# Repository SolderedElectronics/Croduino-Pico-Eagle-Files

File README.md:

# Croduino Pico Eagle Files
## Image

[Croduino Pico(100010)](https://e-radionica.com/en/croduino-pico.html)

## Description and details
Croduino Pico is a sequel to Croduino Basic board. It is simpler than the Basic version since it doesn't have FTDI converter on-board so it needs another board which has one for programming(Croduino Basic, for example). It is imagined to be used for leaving in projects and products.

###Specs:
- Atmega328 microcontroller(32kB flash, 2kB RAM, 0.5kB EEPROM)
- 22 I/O pins, 14 digital I/O, 6 PWM, 8 analog pins
- Size only 3 x 5cm
- LED light on the 13th pin
- Voltage regulator for possibility of external charging
- Made in Croatia (EU)
- Free lifetime technical support at techsupport@e-radionica.com
- Should be set up as "Arduino Nano w/ Atmega328" in Arduino software.

Microcontroller on-board is loaded with Arduino Optiboot bootloader.

## Repository content
This repo contains Cadsoft Eagle .sch and .brd files for Croduino Pico board. It also contains schematic in .pdf created from .sch Eagle file. 
Files have been arranged into folders for navigating between different versions of board. 
Tip: layer 200 shows top silkscreen and layer 208 should be bottom silkscreen. tParts and bParts is not used.

## Docs
- [Croduino Pico product page] (https://e-radionica.com/en/croduino-pico.html)
- [Croduino lessons - on croatian language] (https://vimeo.com/channels/croduino)

## Board versions
- v1.0 - inital version

## License info
This product is open-source. Yay!
For any tech questions, contact us at techsupport@e-radionica.com
If you find an Issue, please open one at GitHub. If you can improve our product, fork us.

e-radionica.com Team.

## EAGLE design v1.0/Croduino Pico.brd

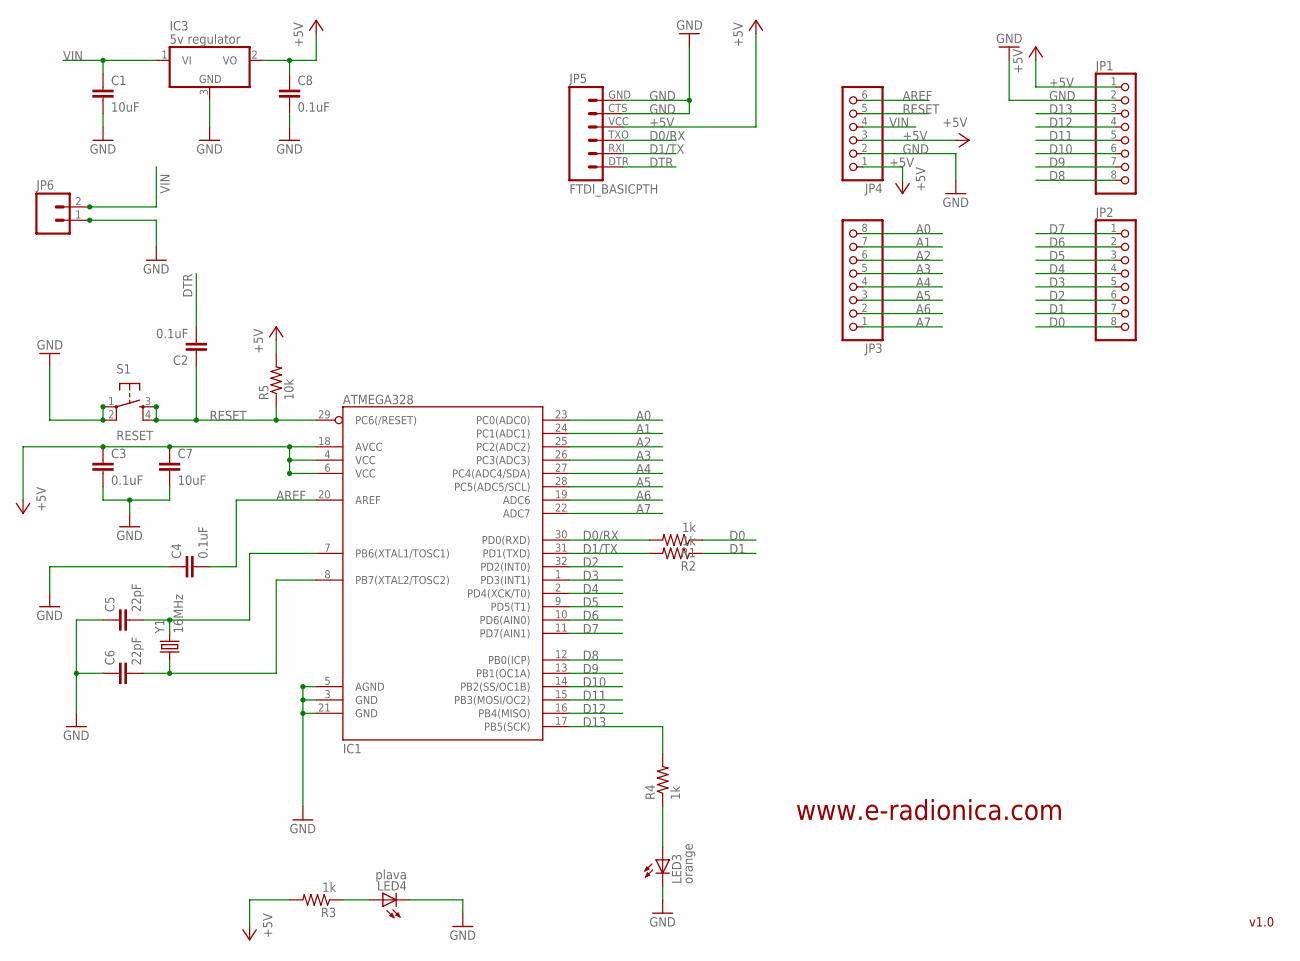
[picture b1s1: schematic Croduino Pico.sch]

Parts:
C1, C7: 10uF; C3216
C2, C3, C4, C8: 0.1uF; 0603-CAP
C5, C6: 22pF; 0603-CAP
IC1: ATMEGA328; TQFP32-08
IC3: 5v regulator; TO252
JP1, JP2, JP3: PINHD-1X8BIG; 1X08-BIG
JP4: PINHD-1X6B; 1X06-BIG
JP5: FTDI_BASICPTH; FTDI_BASIC
JP6: M02LOCK_LONGPADS; 1X02_LOCK_LONGPADS
LED3: orange; CHIP-LED0805
LED4: plava; CHIP-LED0805
R1, R2, R3, R4: 1k; 0603-RES
R5: 10k; 0603-RES
S1: RESET; TACTILE_SWITCH_SMD
Y1: 16MHz; CRYSTAL-SMD-5X3

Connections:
+5V: C3.1, C7.1, C8.1, IC1.4 (VCC), IC1.6 (VCC), IC1.18 (AVCC), IC3.2 (VO), JP1.1, JP4.1, JP4.3, JP5.VCC (4), R3.2, R5.2
A0: IC1.23 (PC0(ADC0)), JP3.8
A1: IC1.24 (PC1(ADC1)), JP3.7
A2: IC1.25 (PC2(ADC2)), JP3.6
A3: IC1.26 (PC3(ADC3)), JP3.5
A4: IC1.27 (PC4(ADC4/SDA)), JP3.4
A5: IC1.28 (PC5(ADC5/SCL)), JP3.3
A6: IC1.19 (ADC6), JP3.2
A7: IC1.22 (ADC7), JP3.1
AREF: C4.2, IC1.20 (AREF), JP4.6
CRYSTAL1: C5.2, IC1.7 (PB6(XTAL1/TOSC1)), Y1.3 (2)
CRYSTAL2: C6.2, IC1.8 (PB7(XTAL2/TOSC2)), Y1.1
D0: JP2.8, R1.1
D0/RX: IC1.30 (PD0(RXD)), JP5.TXO (3), R1.2
D1: JP2.7, R2.1
D1/TX: IC1.31 (PD1(TXD)), JP5.RXI (2), R2.2
D2: IC1.32 (PD2(INT0)), JP2.6
D3: IC1.1 (PD3(INT1)), JP2.5
D4: IC1.2 (PD4(XCK/T0)), JP2.4
D5: IC1.9 (PD5(T1)), JP2.3
D6: IC1.10 (PD6(AIN0)), JP2.2
D7: IC1.11 (PD7(AIN1)), JP2.1
D8: IC1.12 (PB0(ICP)), JP1.8
D9: IC1.13 (PB1(OC1A)), JP1.7
D10: IC1.14 (PB2(SS/OC1B)), JP1.6
D11: IC1.15 (PB3(MOSI/OC2)), JP1.5
D12: IC1.16 (PB4(MISO)), JP1.4
D13: IC1.17 (PB5(SCK)), JP1.3, R4.2
DTR: C2.2, JP5.DTR (1)
GND: C1.2, C3.2, C4.1, C5.1, C6.1, C7.2, C8.2, IC1.3 (GND), IC1.5 (AGND), IC1.21 (GND), IC3.3 (GND), JP1.2, JP4.2, JP5.CTS (5), JP5.GND (6), JP6.1, LED3.C, LED4.C, S1.1, S1.2
unnamed: LED3.A, R4.1
unnamed: LED4.A, R3.1
RESET: C2.1, IC1.29 (PC6(/RESET)), JP4.5, R5.1, S1.3, S1.4
VIN: C1.1, IC3.1 (VI), JP4.4, JP6.2

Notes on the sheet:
v1.0
www.e-radionica.com

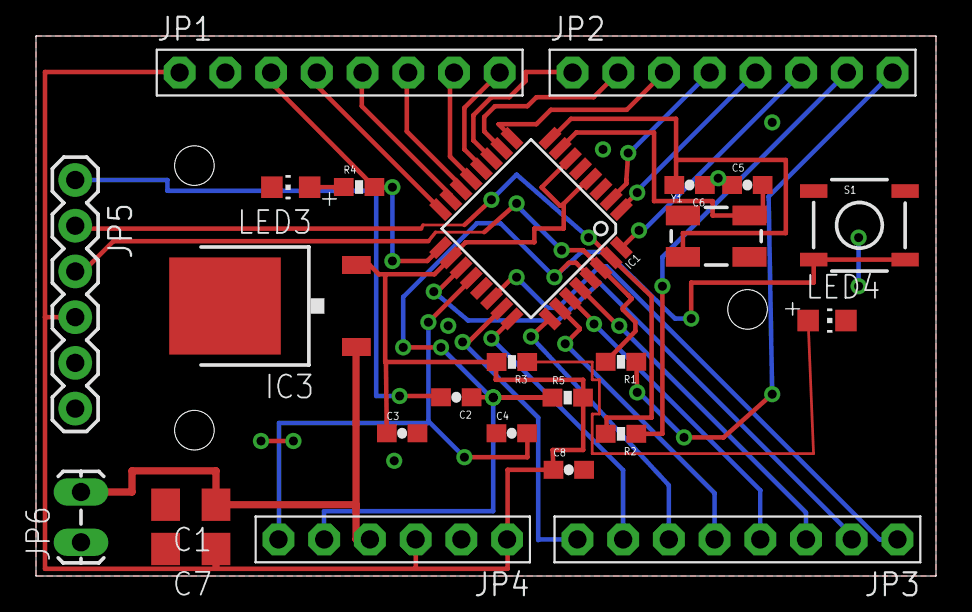
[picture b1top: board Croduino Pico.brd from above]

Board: 2 copper layers, 50.0 x 30.0 mm, 27 parts (0 on the bottom side), 34 nets.

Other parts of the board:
U$1: PICOO
U$2: UTICNICA3MM

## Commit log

2015-08-14 Adding actual files to Repo
2015-08-14 Typing error
2015-08-24 Write Readme, add version folder
2018-11-26 README update

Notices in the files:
parts and their libraries:
SparkFun: Licensing: CC v3.0 Share-Alike You are welcome to use this library for commercial purposes.
